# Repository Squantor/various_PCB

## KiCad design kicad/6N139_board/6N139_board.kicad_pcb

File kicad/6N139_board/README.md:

# 6N139 breakout #
This board is a simple 6N139 breakout board with footprints for all the supporting resistors. These where made to check this circuit and do some experiments. Maybe they are useful for people that want to galvanically digital signals on a budget. They can be ordered on [Oshpark](https://oshpark.com/shared_projects/U0MG0PbD).
## Usage ##
As I generally use 3.3V as much as possible for my projects. These boards have been made with that in mind. As the 6N139 darlington needs to be powered by 4.5V minimum, it has been brought out on a separate pin. The reason for the 220Ohm and 100nF network is to prevent noise coupling back onto the 5V rail. This is useful if you use this setup to couple a sensitive analog domain to a more noisy digital domain. Some projects of mine have a battery powered or highly isolated domain with 22bit ADC's and you want as little fast edges as possible to keep measurement noise down. R1, R3 and R4 values have been determined by the measurements described below.
## Measurement setup and resistor values ##
Some tests have been performed and the optimal resistor values have been determined for my application. Do perform comparable tests to see if they are in line with your expectations/requirements. I have tested these values with the Liteon 6N139's I bought from [reichelt](http://www.reichelt.nl/Optocouplers/6N-139/3/index.html?ACTION=3&GROUPID=3046&ARTICLE=2860&SEARCH=6n139&OFFSET=16&). 
My measurement setup is as follows:

* Philips PM 5785B pulse generator with a 1ns Risetime, Set up at around 100KHz.
* Philips PE 1542 DC powersupply 5V for VCC and 3.3V for I/O pull up voltage.
* Rigol DS1052E modified to 100MHz.

### Resistor values ###
There are 3 main resistors determining performance:

R1: Current limiting resistors for the optocoupler LED. This determines how heavely your output will be loaded. All measurements have been performed with a 1K resistor. The current draw is then around 2.1mA at 3.3V I/O voltage (assuming a led voltage drop of 1.2V).

R3: Base resistor, changes Delaytimes and influences risetime. Smaller resistors increase turn on time, decreases turn off. I have settled for 4.7K to be the best tradeoff with the 1K led resistor R1. The delay times become more or less symmetrical.

R4: Pull up resistor, changes off to on risetime. I have settled for 2.2K to keep the current consumption limited to around 2mA at 3.3V.

### Possible improvements ###
Add a PNP risetime accelerator transistor to improve risetime performance, but this would add complexity. Best to check if your peripherals/devices can handle such slow slopes, or use a separate shmitt trigger to improve risetimes.
### Measurement results ###

Big difference with a china "fairchild" opto.

## Assembled pictures ##

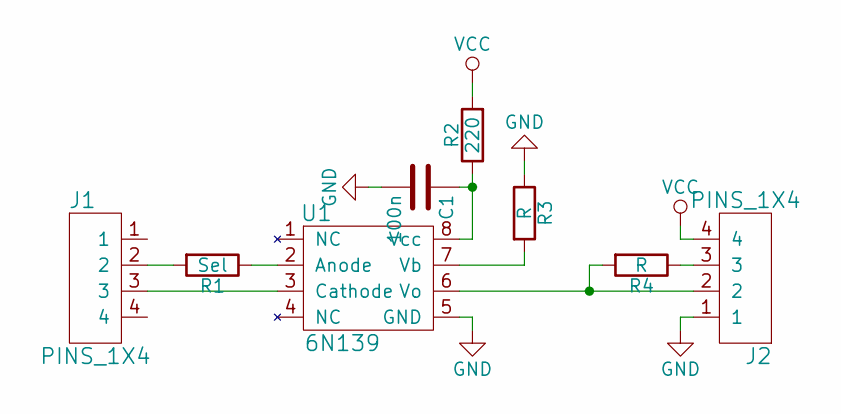
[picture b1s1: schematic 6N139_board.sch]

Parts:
C1: 100n; C_0603
J1, J2: PINS_1X4; Header-2.54-1X04-H1.0
R1: Sel; R_0603
R2: 220; R_0603
R3, R4: R; R_0603
U1: 6N139; DIL08_0.8

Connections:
GND: C1.2, J2.1, R3.1, U1.5 (GND)
unnamed: C1.1, R2.1, U1.8 (Vcc)
unnamed: J1.2, R1.2
unnamed: J1.3, U1.3 (Cathode)
unnamed: J2.2, R4.2, U1.6 (Vo)
unnamed: J2.3, R4.1
unnamed: R1.1, U1.2 (Anode)
unnamed: R3.2, U1.7 (Vb)
VCC: J2.4, R2.2

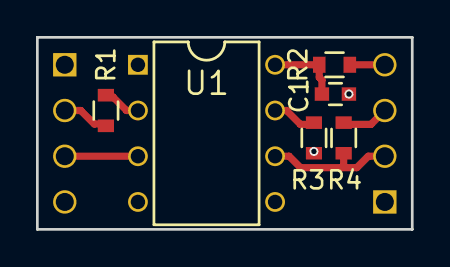
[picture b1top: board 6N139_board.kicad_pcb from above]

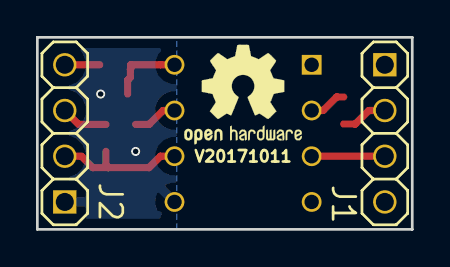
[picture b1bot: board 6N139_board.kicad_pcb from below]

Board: 2 copper layers, 20.8 x 10.7 mm, 8 parts (2 on the bottom side), 9 nets.

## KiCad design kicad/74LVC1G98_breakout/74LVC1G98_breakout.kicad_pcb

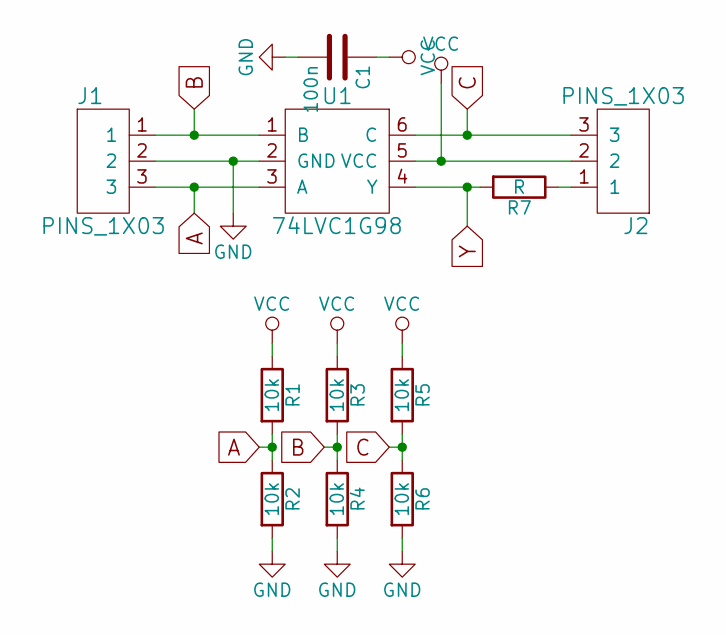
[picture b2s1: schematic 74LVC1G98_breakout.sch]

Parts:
C1: 100n; C_0402
J1: PINS_1X03; Header-0254-1X03-H010
J2: PINS_1X03; Header-0254-1X03-H008
R1, R2, R3, R4, R5, R6: 10k; R_0402_hand
R7: R; R_0402_hand
U1: 74LVC1G98; SOT363

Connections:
A: J1.3, R1.2, R2.1, U1.3 (A)
B: J1.1, R3.2, R4.1, U1.1 (B)
C: J2.3, R5.2, R6.1, U1.6 (C)
GND: C1.2, J1.2, R2.2, R4.2, R6.2, U1.2 (GND)
unnamed: J2.1, R7.1
VCC: C1.1, J2.2, R1.1, R3.1, R5.1, U1.5 (VCC)
Y: R7.2, U1.4 (Y)

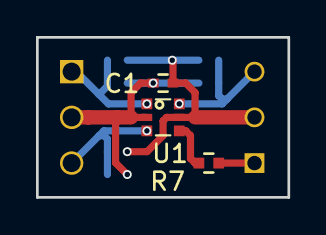
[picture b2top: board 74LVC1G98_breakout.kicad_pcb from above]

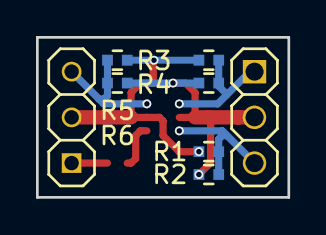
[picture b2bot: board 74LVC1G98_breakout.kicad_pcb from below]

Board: 2 copper layers, 14.0 x 8.9 mm, 11 parts (8 on the bottom side), 7 nets.

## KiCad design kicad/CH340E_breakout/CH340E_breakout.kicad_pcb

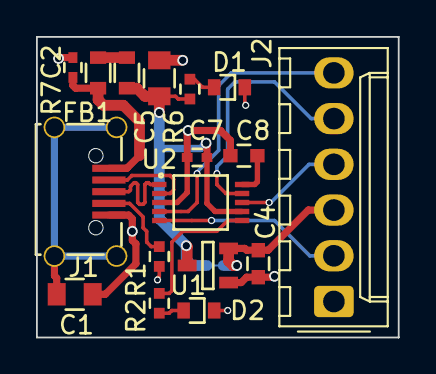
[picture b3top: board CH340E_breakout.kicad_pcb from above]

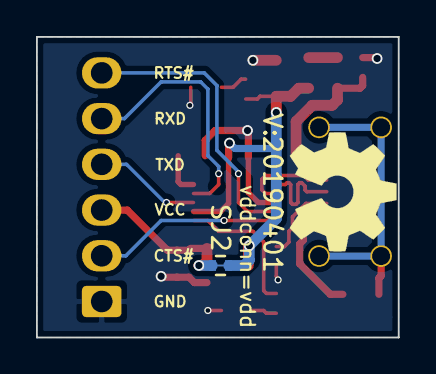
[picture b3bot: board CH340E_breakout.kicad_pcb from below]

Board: 2 copper layers, 20.1 x 16.7 mm, 20 parts (3 on the bottom side), 17 nets.

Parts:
C1: 100n; C_0805
C2, C7: 100n; C_0402
C4, C8: 1u; C_0603
C5: 10u; C_0805
D1, D2: RED; D_0603_hand
FB1: 600; R_0603_hand
J1: USB-ID; USB-muB-SMD_TH
J2: FTDI_PINS_1X06_input; Molex_KK-254_AE-6410-06A_1x06_P2.54mm_Vertical_FTDI_UART
N1: OHWLOGO; OSHW-Symbol_6.7x6mm_SilkScreen
N2: 20190401; Label_version
R1: 0; R_0402_hand
R2, R6: 1K; R_0402_hand
R7: Fuse; R_0603_hand
SJ2: vddconn=vdd; solder_jumper_2way_conn
U1: MCP1702-CB; SOT23-3-Microchip-TT
U2: CH340E; MSOP-10

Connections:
/ACT: R2.2, U2.6
/CTSI: J2.2, U2.5
/RTSO: J2.6, U2.4
/RXI: J2.5, U2.9
/TXO: J2.4, U2.8
/USB_DM: J1.2, U2.2
/USB_DP: J1.3, U2.1
/VBUS: C2.1, J1.1, R7.2
/VDD: C5.1, C7.1, FB1.1, R6.2, SJ2.2, U1.3, U2.7
/VDDCONN: C4.1, J2.3, SJ2.1, U1.2
/VDD_33V: C8.1, U2.10
/VSS: C1.2, C2.2, C4.2, C5.2, C7.2, C8.2, D1.1, D2.1, J1.5, J2.1, R1.2, U1.1, U2.3
unnamed: C1.1, J1.S
unnamed: D1.2, R6.1
unnamed: D2.2, R2.1
unnamed: FB1.2, R7.1
unnamed: J1.4, R1.1

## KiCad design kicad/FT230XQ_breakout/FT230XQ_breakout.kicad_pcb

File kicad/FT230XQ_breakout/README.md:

# FT230XQ breakout
Simple breakout board for the FT230XQ USB to serial converter. The pinout matches the standard FTDI cable pinout but there is also a 4 pin pinout with just RX/TX. Next to the FTDI chip there is also a high current regulator for supplying 3.3V, this is completely separate from VIO of the FTDI so is completely optional. RX, TX and power LED's are present.
## TODO's
Still some things need to be done:
* schematic entry (done)
* PCB layout (done)
* Review with one night in between (done)
* Produce at [OSHPARK](https://oshpark.com/shared_projects/Meu03oe3) (WIP)
* Assemble (TODO)
* Test & characterise (TODO)
* update Readme.md with pictures and BOM (TODO)
## BOM
Due to the general shortage of passive components, where mentioned, just whatever you can find. Mostly 0402 components are used.
* component from [farnell](https://www.farnell.com/)
* Generic resistor in 0402 housing with a value
* Generic capacitor in 0603 housing with a value
## Pictures
TODO

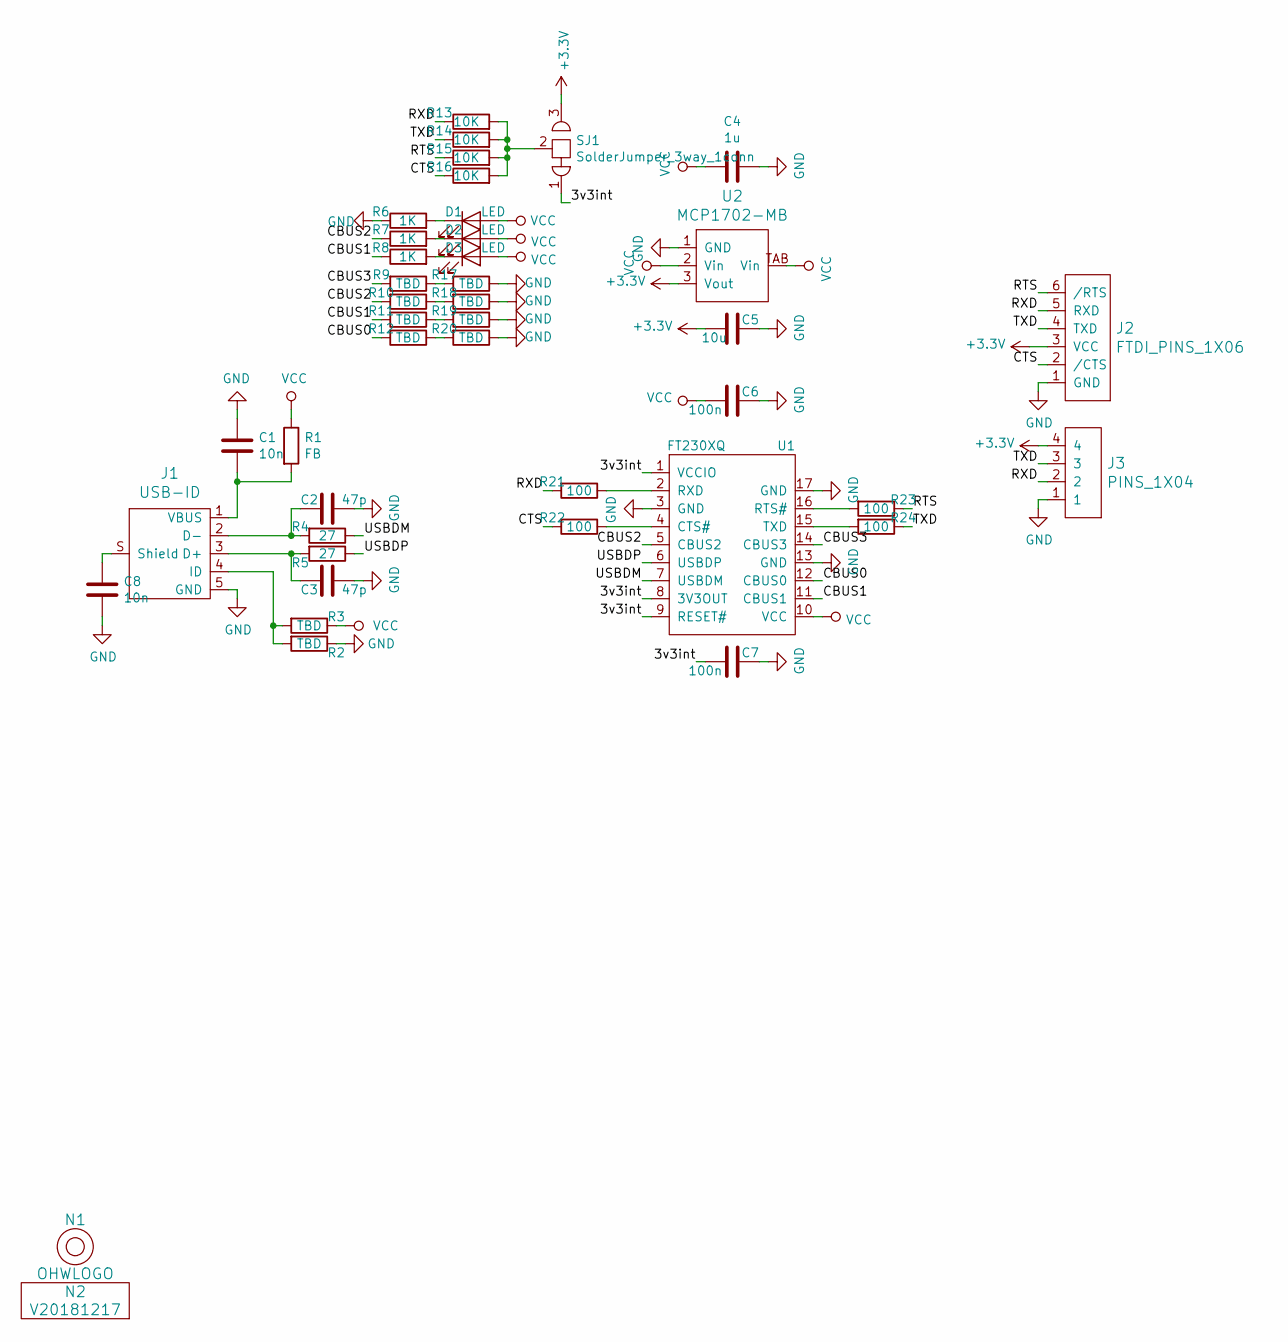
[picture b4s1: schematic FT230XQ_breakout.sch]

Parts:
C1: 10n; C_0603
C2, C3: 47p; C_0402
C4: 1u; C_0603
C5: 10u; C_0805
C6, C7: 100n; C_0402
C8: 10n; C_0805
D1, D2, D3: LED; R_0402_hand
J1: USB-ID; USB-muB-SMD_TH
J2: FTDI_PINS_1X06; Pin_Header_Angled_1x06_Pitch2.54mm
J3: PINS_1X04; Pin_Header_Angled_1x04_Pitch2.54mm
N1: OHWLOGO; OSHW-Symbol_6.7x6mm_SilkScreen
N2: V20181217; Label_version
R1: FB; R_0402_hand
R2, R3, R9, R10, R11, R12, R17, R18, R19, R20: TBD; R_0402_hand
R4, R5: 27; R_0402_hand
R6, R7, R8: 1K; R_0402_hand
R13, R14, R15, R16: 10K; R_0402_hand
R21, R22, R23, R24: 100; R_0402_hand
SJ1: SolderJumper_3way_1conn; solder_jumper_3way_12conn
U1: FT230XQ; QFN_16_4by4mm_FTDI_pad_holes
U2: MCP1702-MB; SOT89-ViaTab-Microchip-MB

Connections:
+3V3: C5.2, J2.3 (VCC), J3.4, SJ1.3, U2.3 (Vout)
/3v3int: C7.2, SJ1.1, U1.1 (VCCIO), U1.8 (3V3OUT), U1.9 (RESET#)
/CBUS0: R12.2, U1.12 (CBUS0)
/CBUS1: R8.1, R11.2, U1.11 (CBUS1)
/CBUS2: R7.1, R10.2, U1.5 (CBUS2)
/CBUS3: R9.2, U1.14 (CBUS3)
/CTS: J2.2 (/CTS), R16.1, R22.2
/RTS: J2.6 (/RTS), R15.1, R23.1
/RXD: J2.5 (RXD), J3.2, R13.1, R21.2
/TXD: J2.4 (TXD), J3.3, R14.1, R24.1
/USBDM: R4.1, U1.7 (USBDM)
/USBDP: R5.1, U1.6 (USBDP)
GND: C1.1, C2.1, C3.1, C4.1, C5.1, C6.1, C7.1, C8.2, J1.5 (GND), J2.1 (GND), J3.1, R3.1, R6.1, R17.1, R18.1, R19.1, R20.1, U1.3 (GND), U1.13 (GND), U1.17 (GND), U2.1 (GND)
unnamed: C1.2, J1.1 (VBUS), R1.2
unnamed: C2.2, J1.2 (D-), R4.2
unnamed: C3.2, J1.3 (D+), R5.2
unnamed: C8.1, J1.S (Shield)
unnamed: D1.1 (K), R6.2
unnamed: D2.1 (K), R7.2
unnamed: D3.1 (K), R8.2
unnamed: J1.4 (ID), R2.2, R3.2
unnamed: R10.1, R18.2
unnamed: R11.1, R19.2
unnamed: R12.1, R20.2
unnamed: R13.2, R14.2, R15.2, R16.2, SJ1.2
unnamed: R9.1, R17.2
unnamed: R21.1, U1.2 (RXD)
unnamed: R22.1, U1.4 (CTS#)
unnamed: R23.2, U1.16 (RTS#)
unnamed: R24.2, U1.15 (TXD)
VCC: C4.2, C6.2, D1.2 (A), D2.2 (A), D3.2 (A), R1.1, R2.1, U1.10 (VCC), U2.2 (Vin), U2.TAB (Vin)

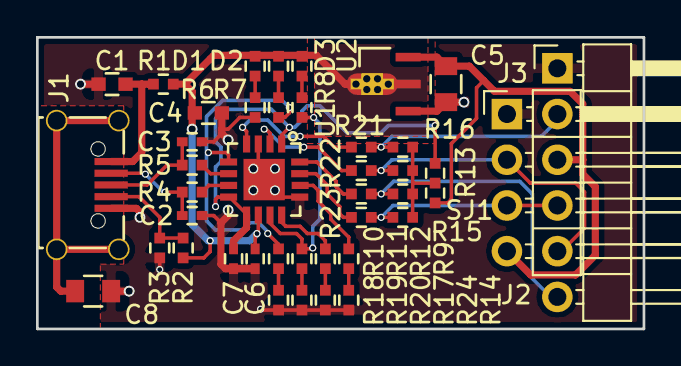
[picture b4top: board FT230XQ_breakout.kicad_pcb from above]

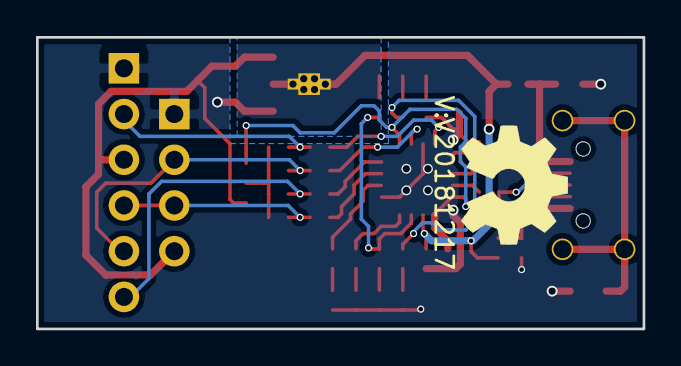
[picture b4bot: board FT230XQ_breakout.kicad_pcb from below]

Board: 2 copper layers, 33.7 x 16.2 mm, 43 parts (2 on the bottom side), 31 nets.

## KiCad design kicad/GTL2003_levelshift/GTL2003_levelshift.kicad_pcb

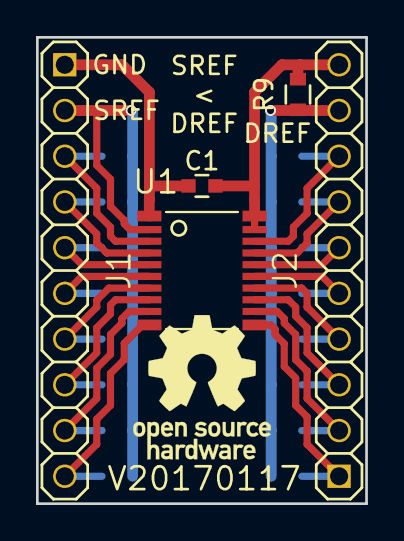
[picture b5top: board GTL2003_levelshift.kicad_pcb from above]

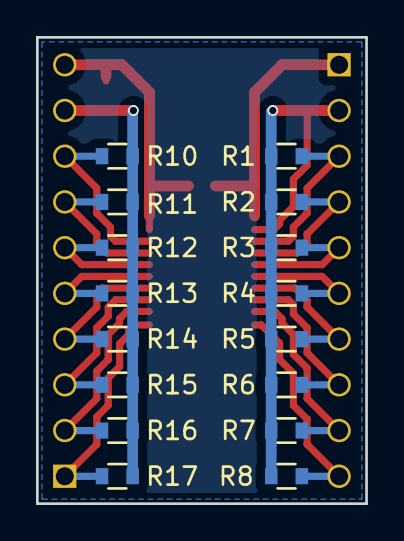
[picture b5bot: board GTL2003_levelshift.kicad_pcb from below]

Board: 2 copper layers, 18.3 x 25.9 mm, 21 parts (16 on the bottom side), 20 nets.

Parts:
C1: 100n; C_0603
J1, J2: PINS_1X10; Header-0254-1X10-H010
R1, R2, R3, R4, R5, R6, R7, R8, R10, R11, R12, R13, R14, R15, R16, R17: PULL; R_0603_hand
R9: R; R_0603_hand
U1: GTL2003; SOT360

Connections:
/D1: J2.8, R10.2, U1.18
/D2: J2.7, R11.2, U1.17
/D3: J2.6, R12.2, U1.16
/D4: J2.5, R13.2, U1.15
/D5: J2.4, R14.2, U1.14
/D6: J2.3, R15.2, U1.13
/D7: J2.2, R16.2, U1.12
/D8: J2.1, R17.2, U1.11
/DREF: J2.9, R9.1, R10.1, R11.1, R12.1, R13.1, R14.1, R15.1, R16.1, R17.1
/GND: C1.2, J1.1, U1.1
/GREF: C1.1, J2.10, R9.2, U1.19, U1.20
/S1: J1.3, R1.2, U1.3
/S2: J1.4, R2.2, U1.4
/S3: J1.5, R3.2, U1.5
/S4: J1.6, R4.2, U1.6
/S5: J1.7, R5.2, U1.7
/S6: J1.8, R6.2, U1.8
/S7: J1.9, R7.2, U1.9
/S8: J1.10, R8.2, U1.10
/SREF: J1.2, R1.1, R2.1, R3.1, R4.1, R5.1, R6.1, R7.1, R8.1, U1.2

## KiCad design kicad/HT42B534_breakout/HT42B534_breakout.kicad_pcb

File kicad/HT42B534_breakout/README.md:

# Holtek HT42B534 breakout board
Breakout board for the [HT42B534-1](https://www.holtek.com/productdetail/-/vg/42B534-x) USB to serial converter. Advantage of the HT42B534 is that it enumerates as a USB CDC device, has programmable EEPROM on board and available in a few tiny packages.
## TODO's
Still some things need to be done:
* schematic entry (TODO)
* PCB layout (TODO)
* Review with one night in between (TODO)
* Produce at [OSHPARK](https://oshpark.com/) (TODO)
* Assemble (TODO)
* Test & characterise (TODO)
* update Readme.md with pictures and BOM (TODO)
## BOM
The HT42B534 can be hard to find but is available from [LCSC](https://lcsc.com/.
* HT42B534-1, [C95344 from LCSC](https://lcsc.com/product-detail/USB_HT42B534-MSOP-10_C95344.html)

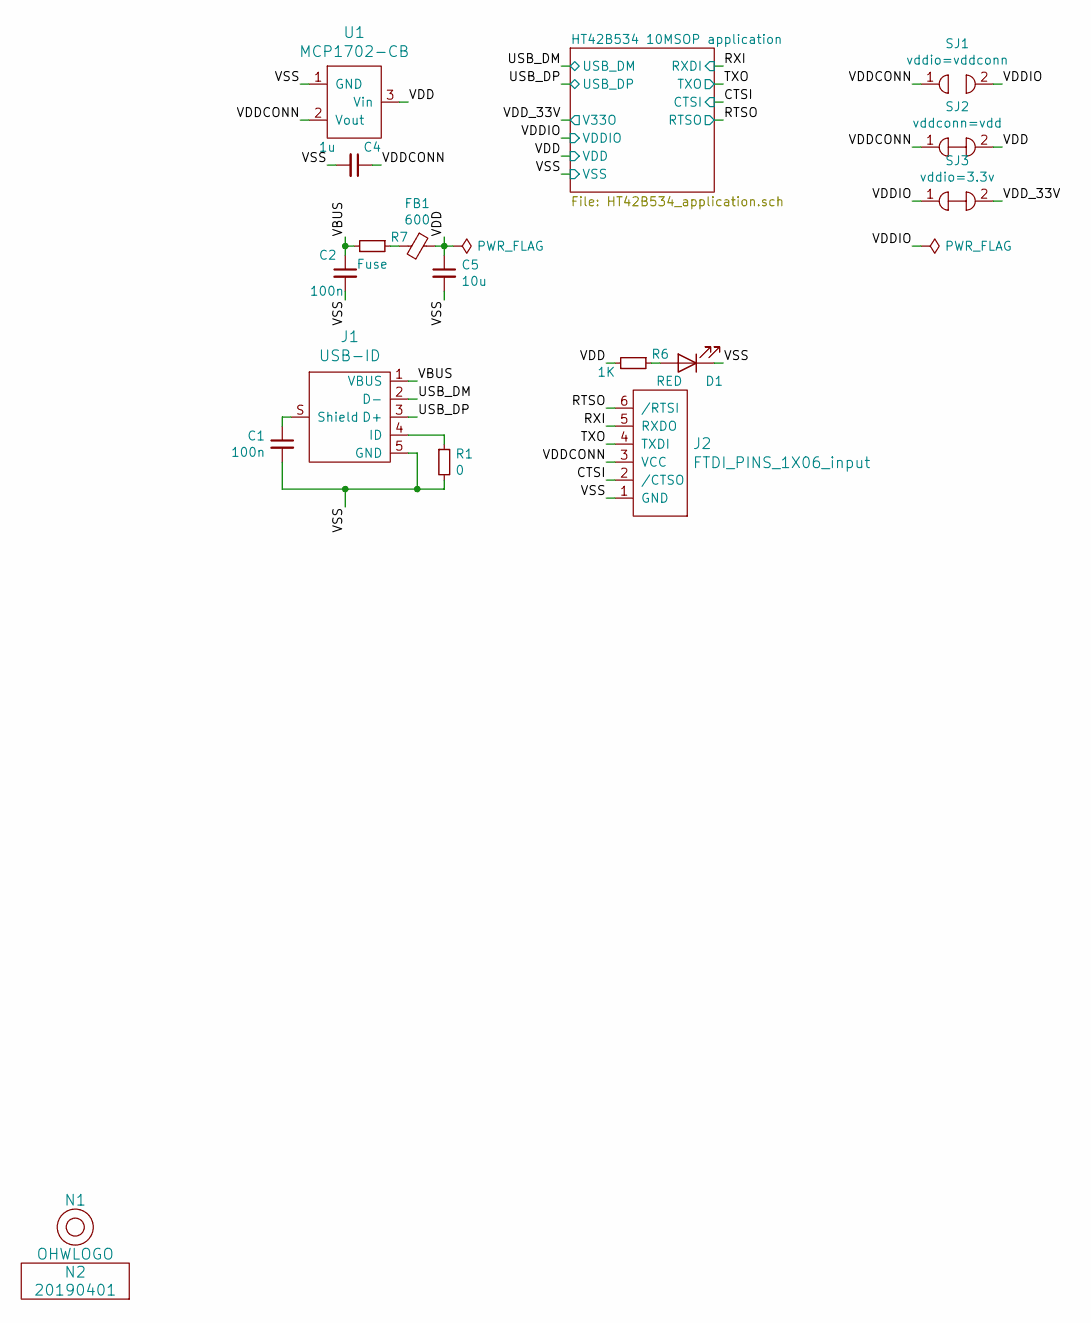
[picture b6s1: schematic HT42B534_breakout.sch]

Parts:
C1: 100n; C_0805
C2: 100n; C_0402
C4: 1u; C_0603
C5: 10u; C_0805
D1: RED; D_0603_hand
FB1: 600; R_0603_hand
J1: USB-ID; USB-muB-SMD_TH
J2: FTDI_PINS_1X06_input; Molex_KK-254_AE-6410-06A_1x06_P2.54mm_Vertical_FTDI_UART
N1: OHWLOGO; OSHW-Symbol_6.7x6mm_SilkScreen
N2: 20190401; Label_version
R1: 0; R_0402_hand
R6: 1K; R_0402_hand
R7: Fuse; R_0603_hand
SJ1: vddio=vddconn; solder_jumper_2way_noconn
SJ2: vddconn=vdd; solder_jumper_2way_conn
SJ3: vddio=3.3v; solder_jumper_2way_conn
U1: MCP1702-CB; SOT23-3-Microchip-TT

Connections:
/CTSI: J2.2 (/CTSO); also elsewhere on the board
/RTSO: J2.6 (/RTSI); also elsewhere on the board
/RXI: J2.5 (RXDO); also elsewhere on the board
/TXO: J2.4 (TXDI); also elsewhere on the board
/USB_DM: J1.2 (D-); also elsewhere on the board
/USB_DP: J1.3 (D+); also elsewhere on the board
/VBUS: C2.1, J1.1 (VBUS), R7.2
/VDD: C5.1, FB1.1, R6.2, SJ2.2, U1.3 (Vin); also elsewhere on the board
/VDDCONN: C4.1, J2.3 (VCC), SJ1.1, SJ2.1, U1.2 (Vout)
/VDDIO: SJ1.2, SJ3.1; also elsewhere on the board
/VDD_33V: SJ3.2; also elsewhere on the board
/VSS: C1.2, C2.2, C4.2, C5.2, D1.1 (K), J1.5 (GND), J2.1 (GND), R1.2, U1.1 (GND); also elsewhere on the board
unnamed: C1.1, J1.S (Shield)
unnamed: D1.2 (A), R6.1
unnamed: FB1.2, R7.1
unnamed: J1.4 (ID), R1.1

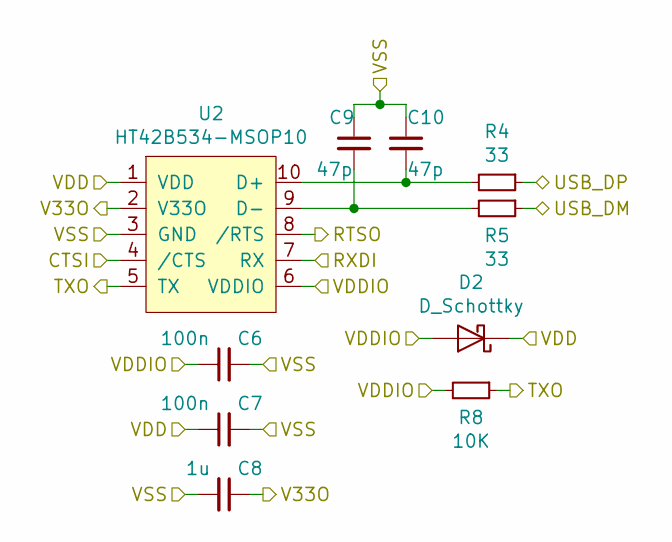
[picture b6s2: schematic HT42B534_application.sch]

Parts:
C6, C7: 100n; C_0402
C8: 1u; C_0603
C9, C10: 47p; C_0402
D2: D_Schottky; SOD-523
R4, R5: 33; R_0402_hand
R8: 10K; R_0402_hand
U2: HT42B534-MSOP10; MSOP-10

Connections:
/CTSI: U2.4 (/CTS); also elsewhere on the board
/RTSO: U2.8 (/RTS); also elsewhere on the board
/RXI: U2.7 (RX); also elsewhere on the board
/TXO: R8.1, U2.5 (TX); also elsewhere on the board
/USB_DM: R5.1; also elsewhere on the board
/USB_DP: R4.1; also elsewhere on the board
/VDD: C7.1, D2.1 (K), U2.1 (VDD); also elsewhere on the board
/VDDIO: C6.1, D2.2 (A), R8.2, U2.6 (VDDIO); also elsewhere on the board
/VDD_33V: C8.1, U2.2 (V33O); also elsewhere on the board
/VSS: C6.2, C7.2, C8.2, C9.1, C10.1, U2.3 (GND); also elsewhere on the board
unnamed: C9.2, R5.2, U2.9 (D-)
unnamed: C10.2, R4.2, U2.10 (D+)

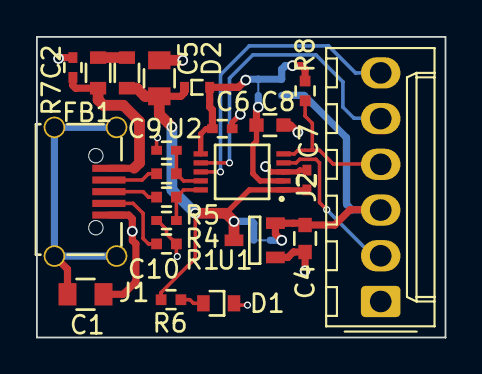
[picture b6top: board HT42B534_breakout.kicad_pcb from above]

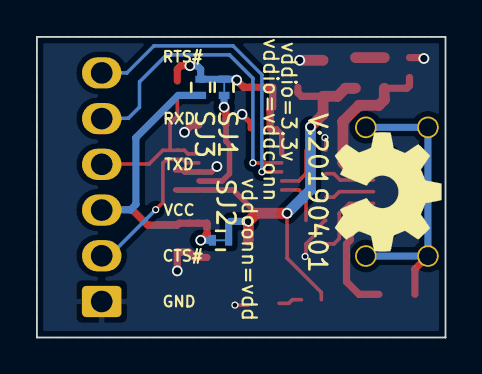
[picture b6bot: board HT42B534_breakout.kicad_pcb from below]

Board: 2 copper layers, 22.7 x 16.7 mm, 27 parts (5 on the bottom side), 18 nets.
